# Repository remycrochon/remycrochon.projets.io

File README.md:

# Projets-Diy
Mise à disposition de mes projets conçus sous Eagle

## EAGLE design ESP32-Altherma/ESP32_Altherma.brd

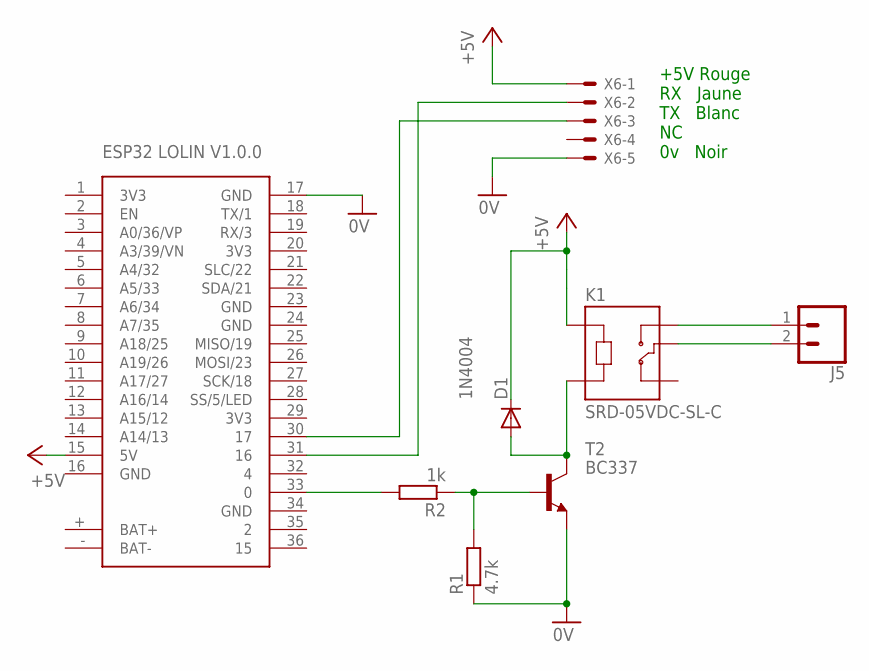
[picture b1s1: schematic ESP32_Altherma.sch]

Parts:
D1: 1N4004; DO41-10
J5: CONN_025MM; BORNIER_A_VIS_2_5.12MM
K1: SRD-05VDC-SL-C; RELAY_SRD-05VDC-SL-C
R1: 4.7k; 0207/10
R2: 1k; 0207/10
T2: BC337; TO92
U$4: ESP32_LOLIN_V1.0.0
X6: JST-XH-05-PIN-LONG-PAD; JST-XH-05-PACKAGE-LONG-PAD

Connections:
0V: R1.1, T2.1 (E), U$4.17 (GND), X6.5
3V3: U$4.1 (3V3), U$4.20 (3V3), U$4.29 (3V3)
+5V: D1.C, K1.A1, U$4.15 (5V), X6.1
BAT+: U$4.+ (BAT+)
BAT-: U$4.- (BAT-)
GND: U$4.16 (GND), U$4.23 (GND), U$4.24 (GND), U$4.34 (GND)
unnamed: D1.A, K1.A2, T2.3 (C)
unnamed: U$4.31 (16), X6.2
unnamed: U$4.30 (17), X6.3
unnamed: J5.1, K1.NO
unnamed: J5.2, K1.COM
unnamed: R1.2, R2.1, T2.2 (B)
unnamed: R2.2, U$4.33 (0)

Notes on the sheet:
+5V Rouge RX Jaune TX Blanc NC 0v Noir

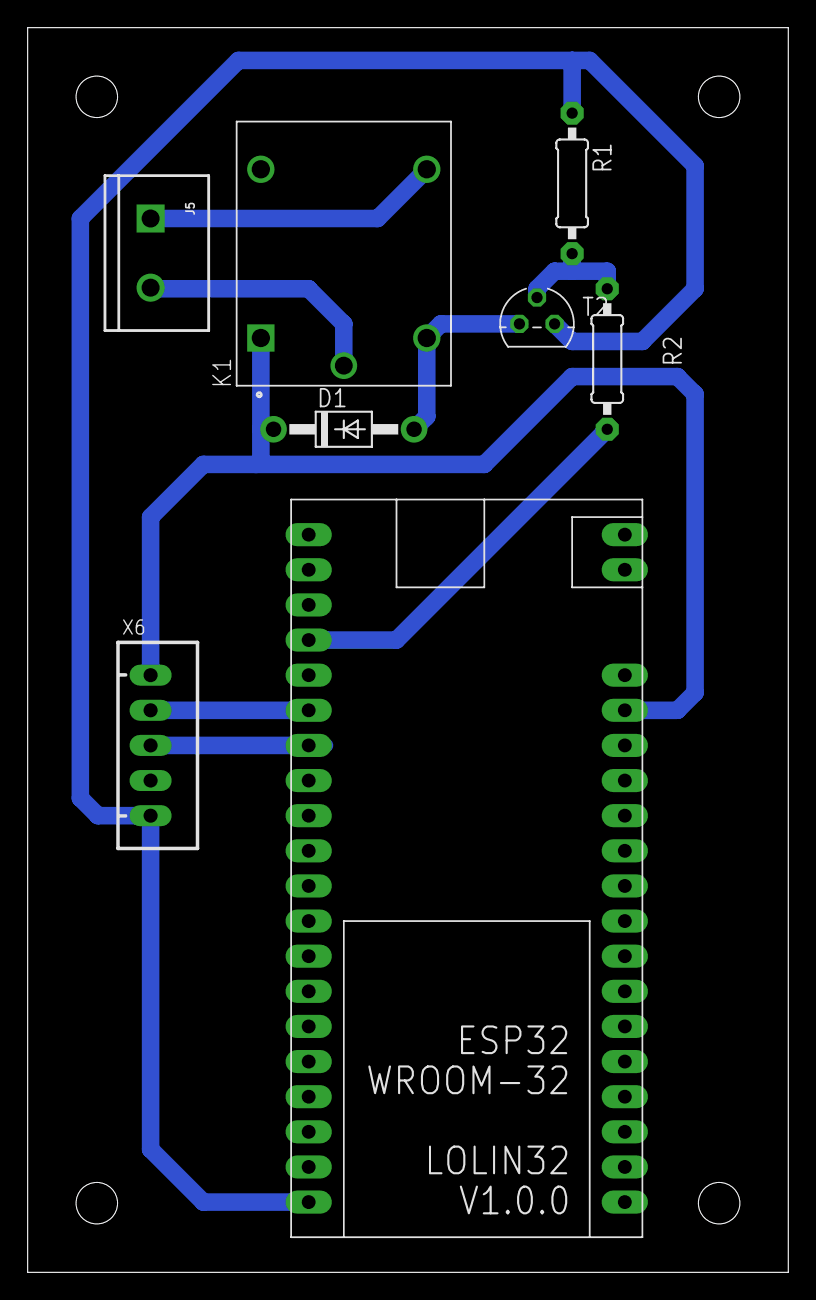
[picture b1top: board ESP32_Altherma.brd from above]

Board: 2 copper layers, 55.0 x 90.0 mm, 8 parts (0 on the bottom side), 11 nets.

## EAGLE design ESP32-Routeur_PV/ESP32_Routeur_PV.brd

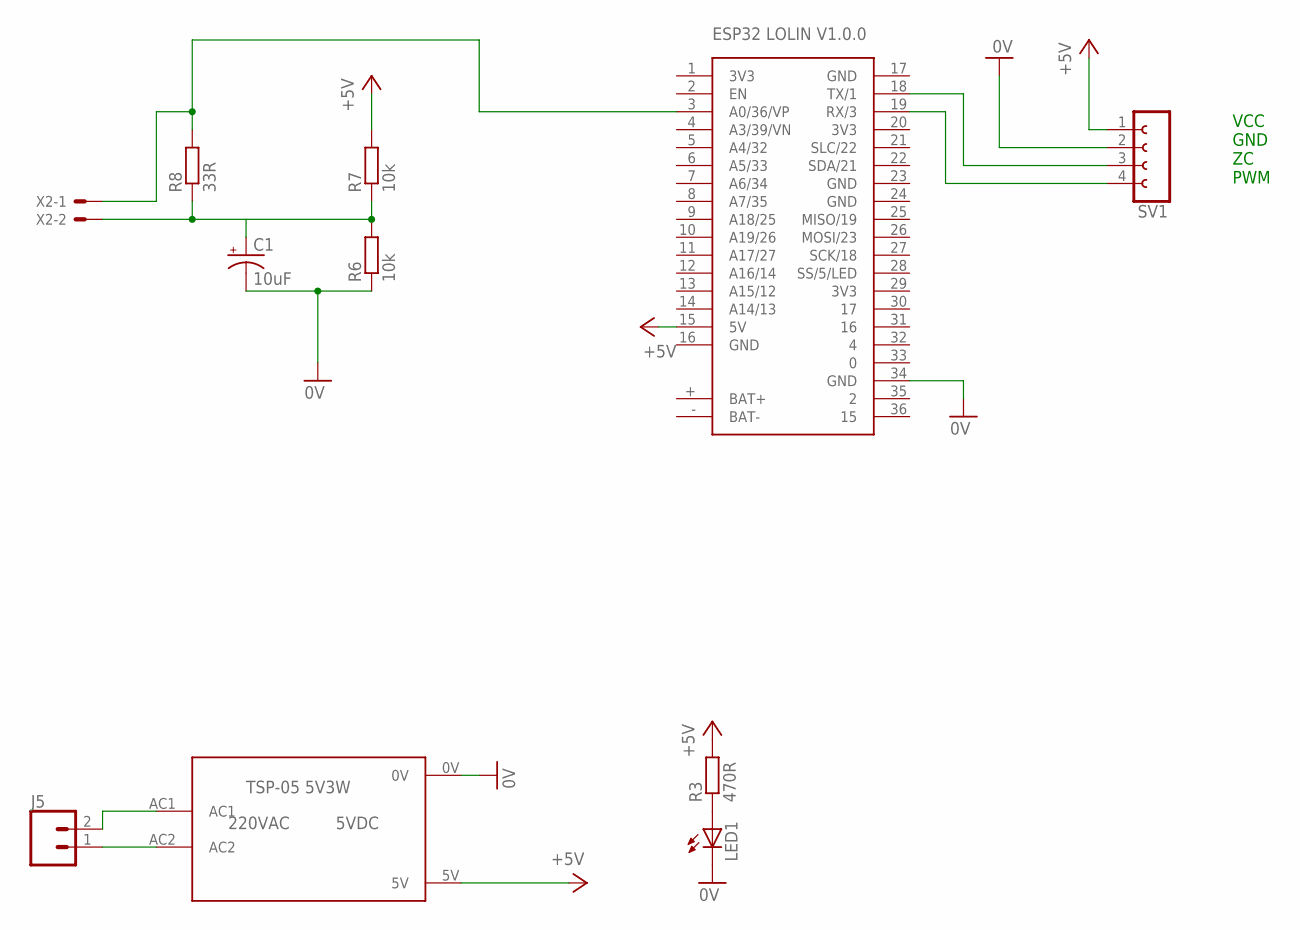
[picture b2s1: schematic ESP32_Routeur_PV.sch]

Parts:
C1: 10uF; CPOL-RADIAL-2.5MM-5MM
J5: CONN_025MM; BORNIER_A_VIS_2_5.12MM
LED1: LED5MM_F; LED5MM
R3: 470R; 0207/10
R6, R7: 10k; 0207/10
R8: 33R; 0207/10
SV1: FE04-1
U$3: TSP05-5V-3W
U$4: ESP32_LOLIN_V1.0.0
X2: JST-XH-02-PIN-LONG-PAD; JST-XH-02-PACKAGE-LONG-PAD

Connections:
0V: C1.2 (-), LED1.K (C), R6.1, SV1.2, U$3.0V, U$4.34 (GND)
3V3: U$4.1 (3V3), U$4.20 (3V3), U$4.29 (3V3)
+5V: R3.2, R7.2, SV1.1, U$3.5V, U$4.15 (5V)
BAT+: U$4.+ (BAT+)
BAT-: U$4.- (BAT-)
GND: U$4.16 (GND), U$4.17 (GND), U$4.23 (GND), U$4.24 (GND)
unnamed: LED1.A, R3.1
unnamed: C1.1 (+), R6.2, R7.1, R8.1, X2.2
unnamed: SV1.3, U$4.18 (TX/1)
unnamed: SV1.4, U$4.19 (RX/3)
unnamed: J5.2, U$3.AC1
unnamed: J5.1, U$3.AC2
unnamed: R8.2, U$4.3 (A0/36/VP), X2.1

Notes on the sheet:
VCC GND ZC PWM

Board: 2 copper layers, 11 parts (1 on the bottom side), 11 nets, no tracks yet.

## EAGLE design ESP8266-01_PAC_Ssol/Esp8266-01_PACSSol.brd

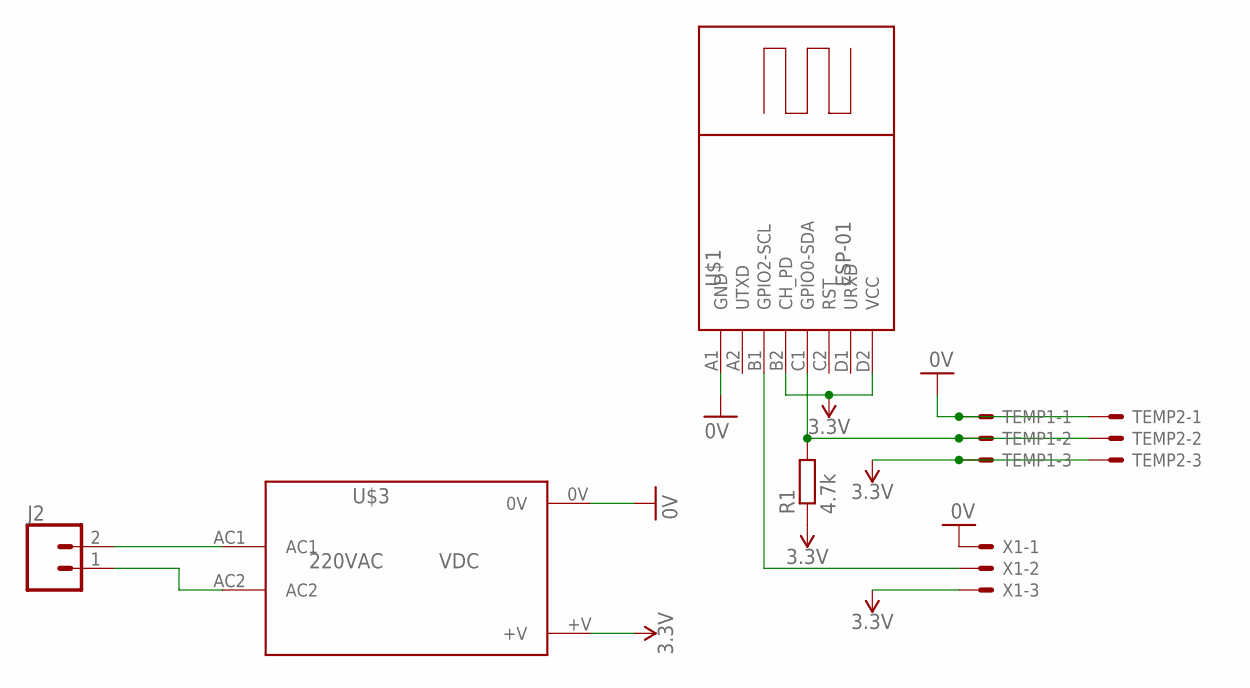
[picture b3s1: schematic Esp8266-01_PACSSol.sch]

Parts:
J2: CONN_025MM; BORNIER_A_VIS_2_5.12MM
R1: 4.7k; 0207/10
TEMP1, TEMP2: JST-XH-03-PIN-LONG-PAD; JST-XH-03-PACKAGE-LONG-PAD
U$1: ESP-01
U$3: TSP05-5V-3W; TSP05-VDC-3W
X1: JST-XH-03-PIN-LONG-PAD; JST-XH-03-PACKAGE-LONG-PAD

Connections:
0V: TEMP1.1, TEMP2.1, U$1.A1 (GND), U$3.0V, X1.1
3.3V: R1.1, TEMP1.3, TEMP2.3, U$1.B2 (CH_PD), U$1.D2 (VCC), U$3.+V, X1.3
unnamed: J2.2, U$3.AC1
unnamed: J2.1, U$3.AC2
unnamed: U$1.B1 (GPIO2-SCL), X1.2
unnamed: R1.2, TEMP1.2, TEMP2.2, U$1.C1 (GPIO0-SDA)

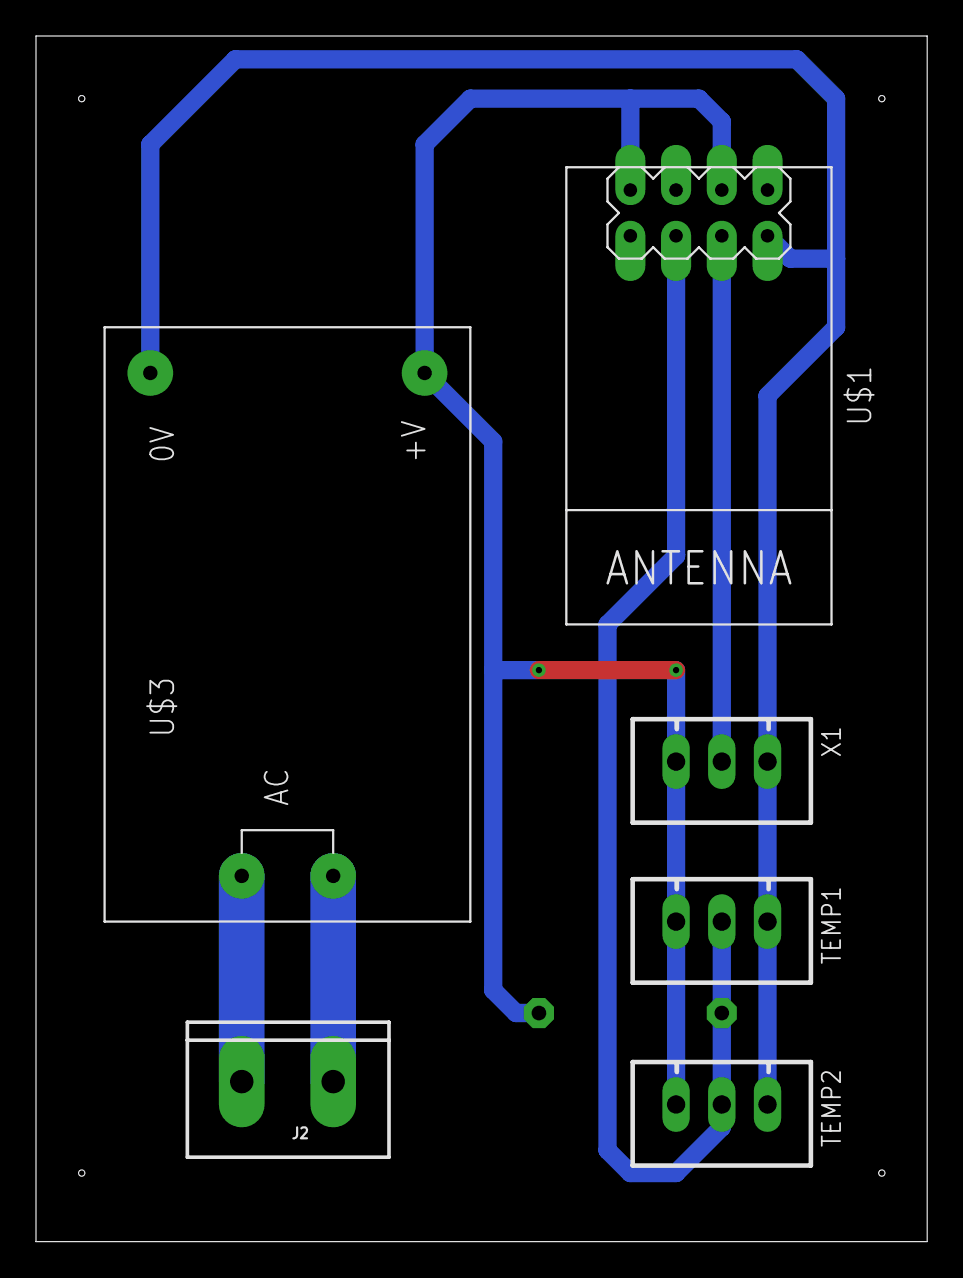
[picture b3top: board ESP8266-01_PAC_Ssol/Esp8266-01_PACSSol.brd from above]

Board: 2 copper layers, 49.5 x 67.0 mm, 7 parts (1 on the bottom side), 6 nets.

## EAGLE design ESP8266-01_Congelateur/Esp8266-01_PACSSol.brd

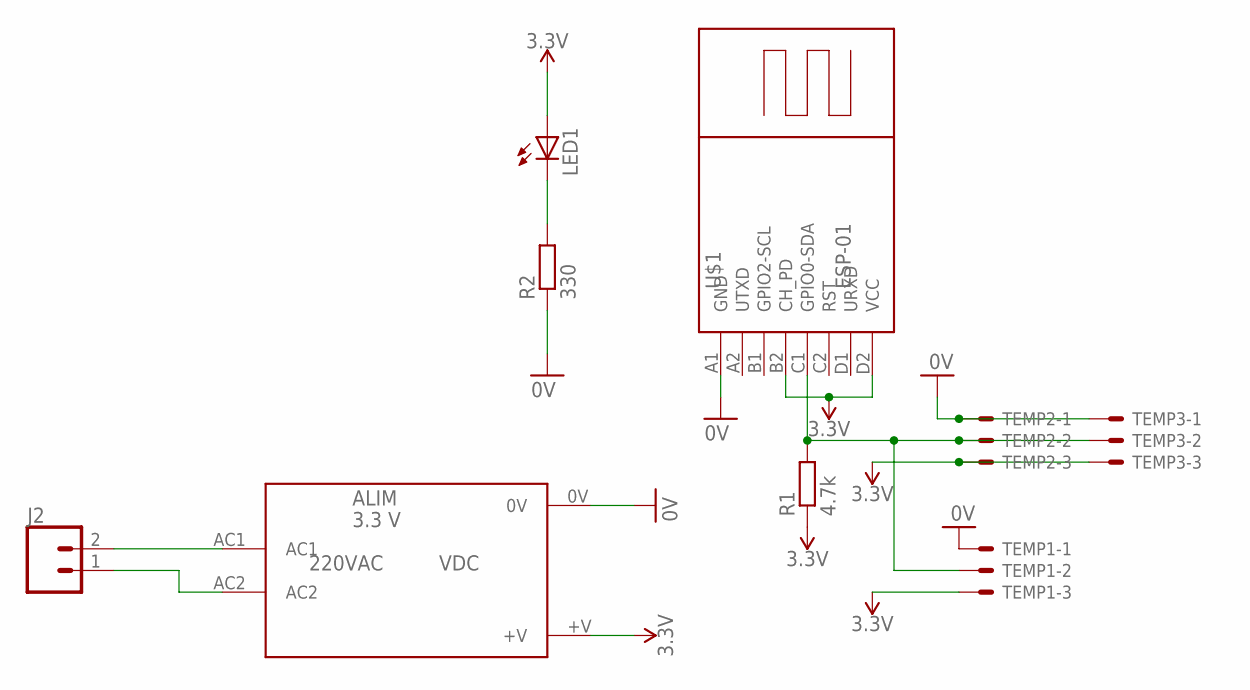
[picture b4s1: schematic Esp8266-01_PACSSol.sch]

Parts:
ALIM: 3.3 V; TSP05-VDC-3W
J2: CONN_025MM; BORNIER_A_VIS_2_5.12MM
LED1: LED5MM_F; LED5MM
R1: 4.7k; 0207/10
R2: 330; 0207/10
TEMP1, TEMP2, TEMP3: JST-XH-03-PIN-LONG-PAD; JST-XH-03-PACKAGE-LONG-PAD
U$1: ESP-01

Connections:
0V: ALIM.0V, R2.1, TEMP1.1, TEMP2.1, TEMP3.1, U$1.A1 (GND)
3.3V: ALIM.+V, LED1.A, R1.1, TEMP1.3, TEMP2.3, TEMP3.3, U$1.B2 (CH_PD), U$1.D2 (VCC)
unnamed: ALIM.AC1, J2.2
unnamed: ALIM.AC2, J2.1
unnamed: LED1.K (C), R2.2
unnamed: R1.2, TEMP1.2, TEMP2.2, TEMP3.2, U$1.C1 (GPIO0-SDA)

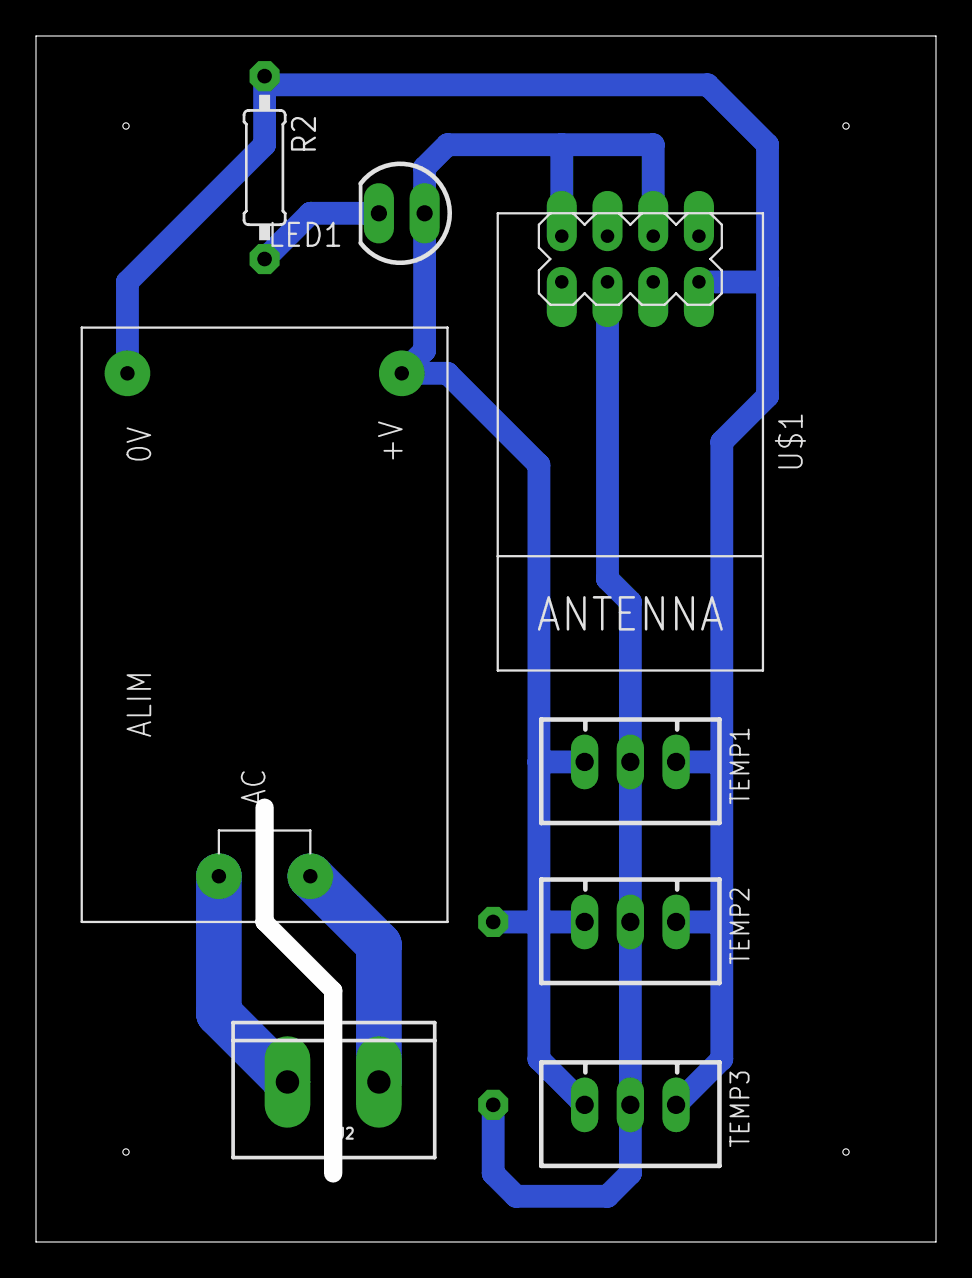
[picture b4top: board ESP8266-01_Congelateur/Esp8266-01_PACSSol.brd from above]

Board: 2 copper layers, 49.0 x 66.0 mm, 9 parts (1 on the bottom side), 6 nets.

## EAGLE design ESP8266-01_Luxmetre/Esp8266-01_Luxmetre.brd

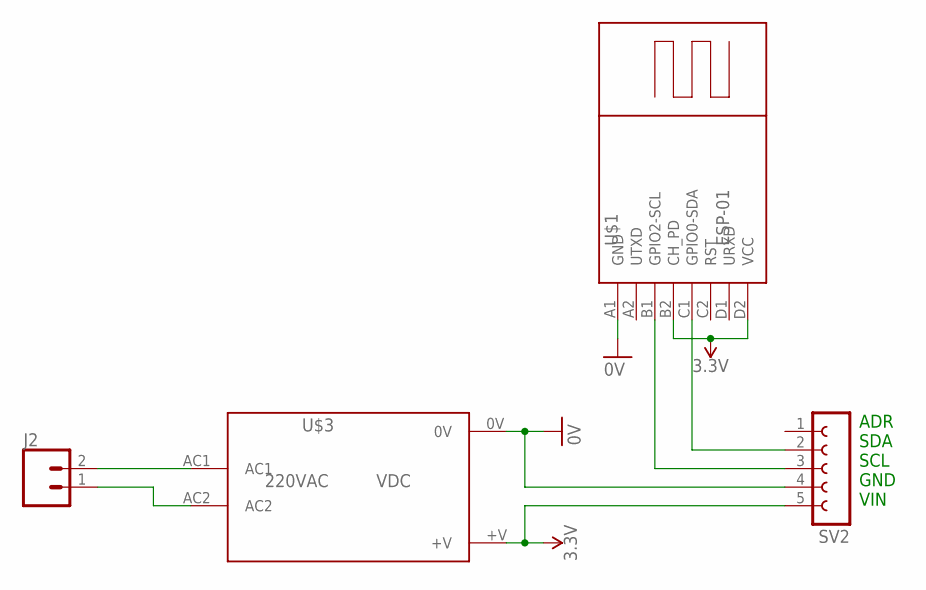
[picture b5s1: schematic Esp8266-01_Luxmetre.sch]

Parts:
J2: CONN_025MM; BORNIER_A_VIS_2_5.12MM
SV2: FE05-1
U$1: ESP-01
U$3: TSP05-5V-3W; TSP05-VDC-3W

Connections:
0V: SV2.4, U$1.A1 (GND), U$3.0V
3.3V: SV2.5, U$1.B2 (CH_PD), U$1.D2 (VCC), U$3.+V
unnamed: J2.2, U$3.AC1
unnamed: J2.1, U$3.AC2
unnamed: SV2.3, U$1.B1 (GPIO2-SCL)
unnamed: SV2.2, U$1.C1 (GPIO0-SDA)

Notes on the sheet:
ADR SDA SCL GND VIN

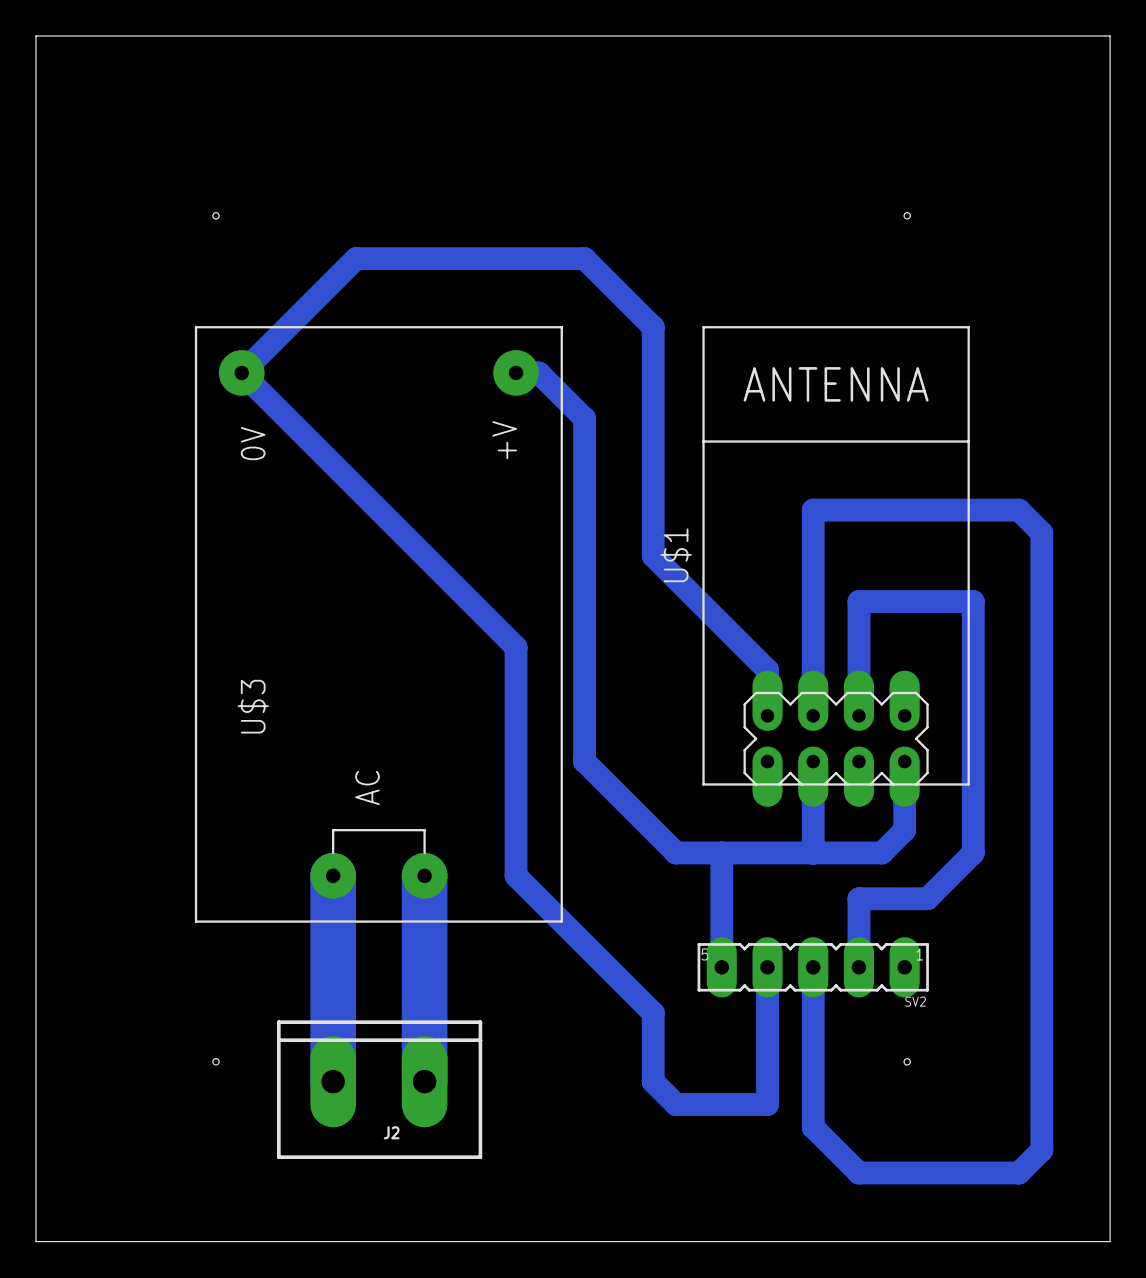
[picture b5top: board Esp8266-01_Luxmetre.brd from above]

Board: 2 copper layers, 59.7 x 67.0 mm, 4 parts (0 on the bottom side), 6 nets.

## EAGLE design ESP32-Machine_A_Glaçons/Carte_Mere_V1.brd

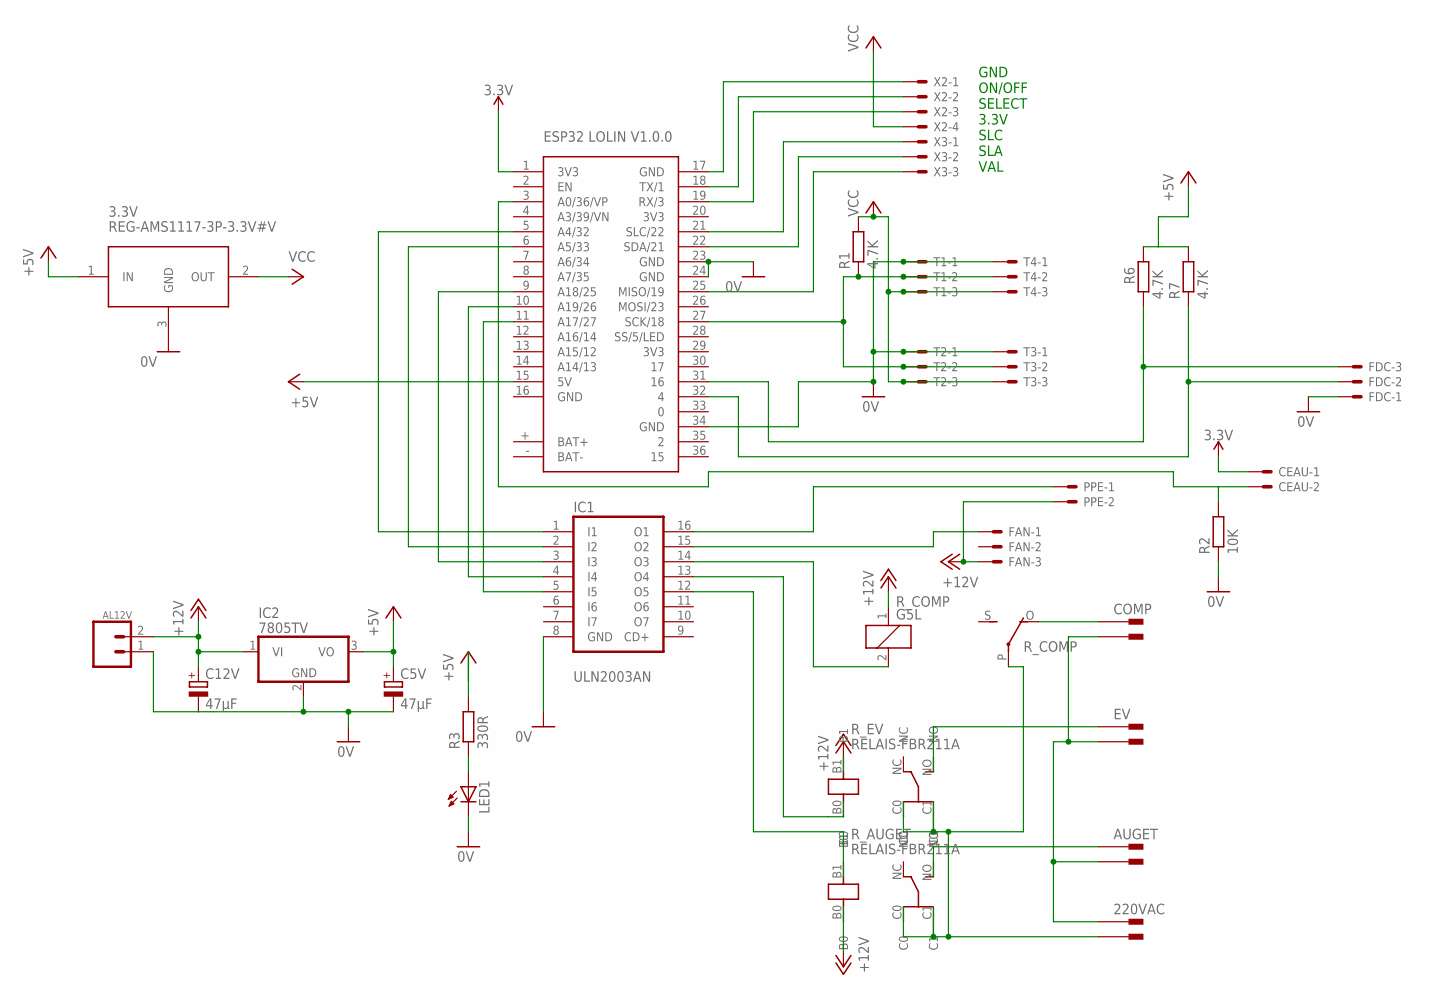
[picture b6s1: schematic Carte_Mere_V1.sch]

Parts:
3.3V: REG-AMS1117-3P-3.3V#V; REG-AMS1117-3P#V
220VAC, 220VAC_N: PIN2F061.040; F061.040
AL12V: CONN_025MM; BORNIER_A_VIS_2_5.12MM
AUGET: PIN2F061.040; F061.040
AUGET_N: PIN2F061.040; F061.040
C5V, C12V: 47µF; E2,5-5
CEAU: JST-XH-02-PIN-LONG-PAD; JST-XH-02-PACKAGE-LONG-PAD
COMP: PIN2F061.040; F061.040
COMP_N: PIN2F061.040; F061.040
EV: PIN2F061.040; F061.040
EV_N: PIN2F061.040; F061.040
FAN: JST-XH-03-PIN-LONG-PAD; JST-XH-03-PACKAGE-LONG-PAD
FDC: JST-XH-03-PIN-LONG-PAD; JST-XH-03-PACKAGE-LONG-PAD
IC1: ULN2003AN; DIL16
IC2: 7805TV; TO220V
LED1: LED5MM_F; LED5MM
PPE: JST-XH-02-PIN-LONG-PAD; JST-XH-02-PACKAGE-LONG-PAD
R1, R6, R7: 4.7K; 0207/10
R2: 10K; 0207/10
R3: 330R; 0207/10
R_AUGET: RELAIS-FBR211A
R_COMP: G5L; G5LE
R_EV: RELAIS-FBR211A
T1, T2, T3, T4: JST-XH-03-PIN-LONG-PAD; JST-XH-03-PACKAGE-LONG-PAD
U$1: ESP32_LOLIN_V1.0.0
X2: JST-XH-04-PIN-LONG-PAD; JST-XH-04-PACKAGE-LONG-PAD
X3: JST-XH-03-PIN-LONG-PAD; JST-XH-03-PACKAGE-LONG-PAD

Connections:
0V: 3.3V.3 (GND), AL12V.1, C5V.V-, C12V.V-, FDC.1, IC1.8 (GND), IC2.2 (GND), LED1.K (C), R2.1, T1.1, T2.1, T3.1, T4.1, U$1.23 (GND), U$1.24 (GND), U$1.34 (GND)
3.3V: CEAU.1, U$1.1 (3V3)
3V3: U$1.20 (3V3), U$1.29 (3V3)
+5V: 3.3V.1 (IN), C5V.V+, IC2.3 (VO), R3.2, R6.2, R7.2, U$1.15 (5V)
+12V: AL12V.2, C12V.V+, FAN.3, IC2.1 (VI), PPE.2, R_AUGET.B0, R_COMP.1, R_EV.B1
BAT+: U$1.+ (BAT+)
BAT-: U$1.- (BAT-)
GND: U$1.16 (GND)
unnamed: U$1.21 (SLC/22), X3.1
unnamed: EV.A1, EV.A2, R_EV.NO
unnamed: IC1.1 (I1), U$1.5 (A4/32)
unnamed: FDC.2, R7.1, U$1.32 (4)
unnamed: IC1.2 (I2), U$1.6 (A5/33)
unnamed: LED1.A, R3.1
unnamed: IC1.16 (O1), PPE.1
unnamed: FAN.1, IC1.15 (O2)
unnamed: IC1.14 (O3), R_COMP.2
unnamed: IC1.3 (I3), U$1.9 (A18/25)
unnamed: IC1.4 (I4), U$1.10 (A19/26)
unnamed: IC1.5 (I5), U$1.11 (A17/27)
unnamed: IC1.13 (O4), R_EV.B0
unnamed: IC1.12 (O5), R_AUGET.B1
unnamed: 220VAC.A1, 220VAC.A2, AUGET_N.A1, AUGET_N.A2, COMP_N.A1, COMP_N.A2, EV_N.A1, EV_N.A2
unnamed: U$1.22 (SDA/21), X3.2
unnamed: AUGET.A1, AUGET.A2, R_AUGET.NO
unnamed: COMP.A1, COMP.A2, R_COMP.O
unnamed: 220VAC_N.A1, 220VAC_N.A2, R_AUGET.C0, R_AUGET.C1, R_COMP.P, R_EV.C0, R_EV.C1
unnamed: U$1.17 (GND), X2.1
unnamed: FDC.3, R6.1, U$1.31 (16)
unnamed: U$1.18 (TX/1), X2.2
unnamed: U$1.19 (RX/3), X2.3
unnamed: U$1.25 (MISO/19), X3.3
unnamed: CEAU.2, R2.2, U$1.3 (A0/36/VP)
unnamed: R1.1, T1.2, T2.2, T3.2, T4.2, U$1.27 (SCK/18)
VCC: 3.3V.2 (OUT), R1.2, T1.3, T2.3, T3.3, T4.3, X2.4

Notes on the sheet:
GND ON/OFF SELECT 3.3V SLC SLA VAL

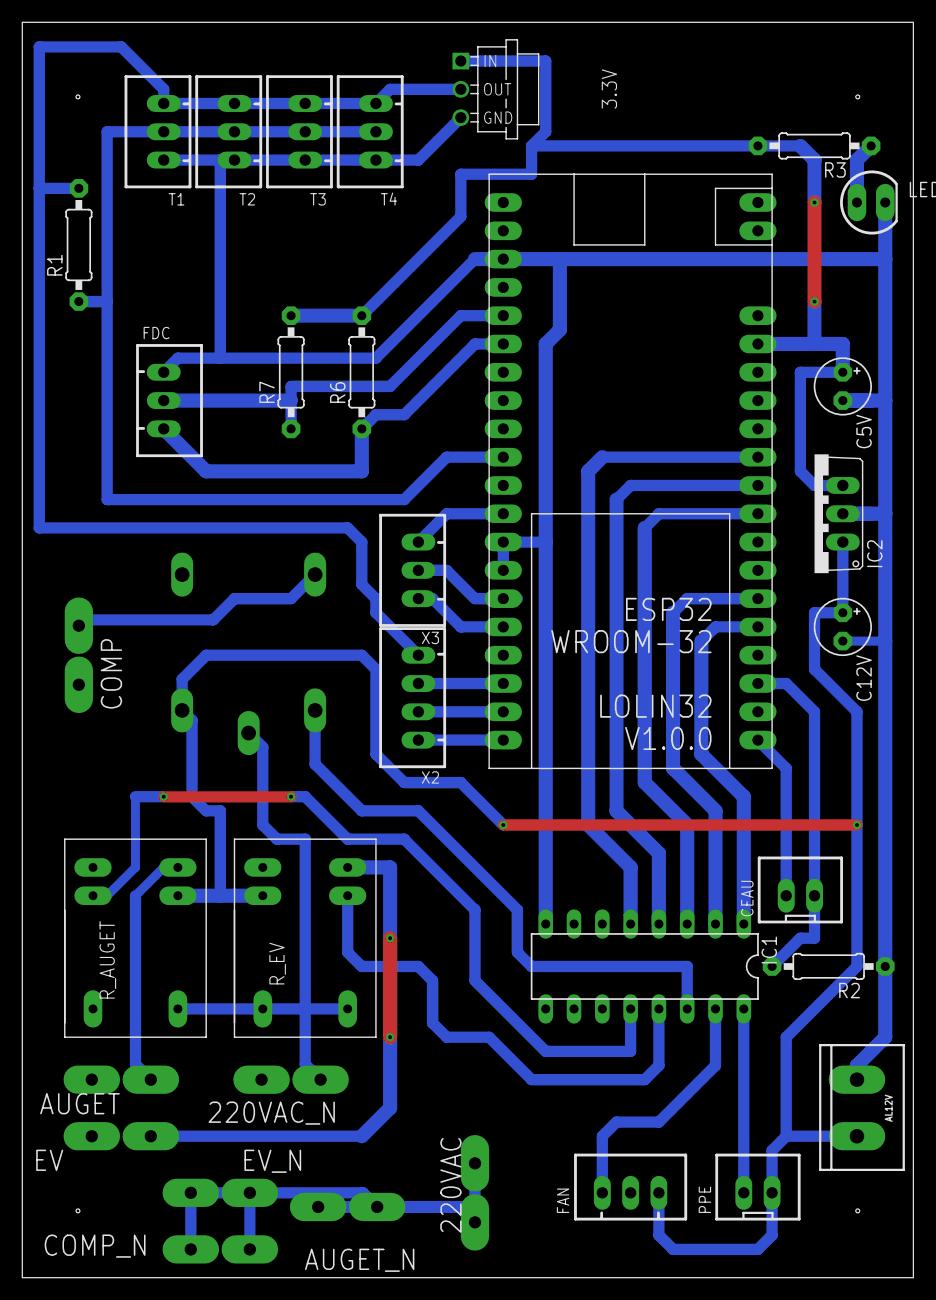
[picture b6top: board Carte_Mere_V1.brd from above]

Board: 2 copper layers, 80.0 x 112.7 mm, 34 parts (1 on the bottom side), 32 nets.

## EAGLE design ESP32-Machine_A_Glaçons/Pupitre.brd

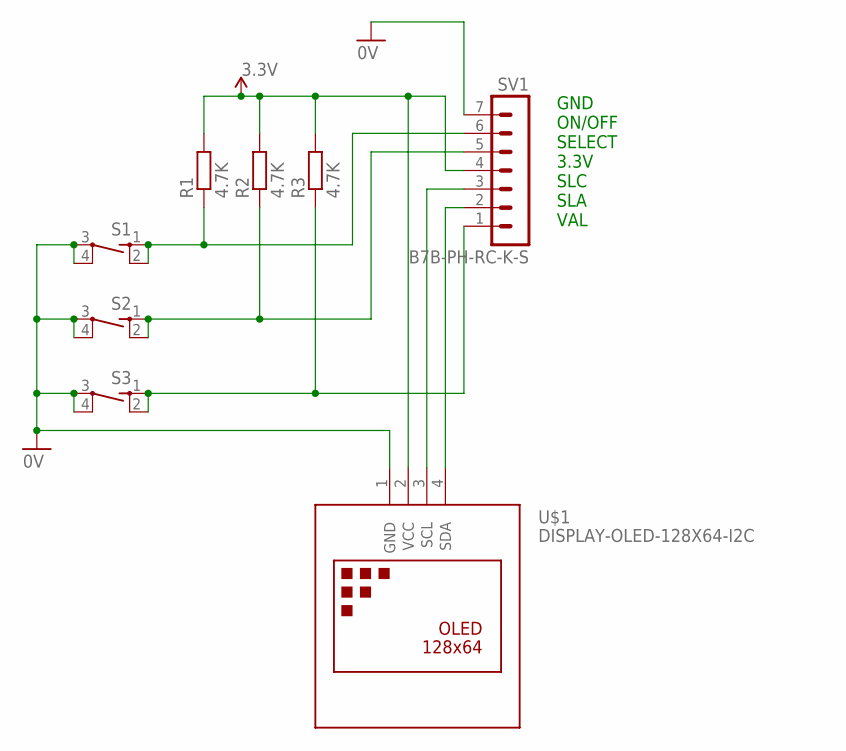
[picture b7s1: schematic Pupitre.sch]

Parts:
R1, R2, R3: 4.7K; 0207/10
S1, S2, S3: SWITCH_10-XX; SWITCH-10XX
SV1: B7B-PH-RC-K-S; B7B-PH-K-S
U$1: DISPLAY-OLED-128X64-I2C

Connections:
0V: S1.3, S1.4 (P1), S2.3, S2.4 (P1), S3.3, S3.4 (P1), SV1.7, U$1.1 (GND)
unnamed: R3.1, S3.1 (S), S3.2 (S1), SV1.1
unnamed: R2.1, S2.1 (S), S2.2 (S1), SV1.5
unnamed: R1.1, S1.1 (S), S1.2 (S1), SV1.6
unnamed: R1.2, R2.2, R3.2, SV1.4, U$1.2 (VCC)
unnamed: SV1.2, U$1.4 (SDA)
unnamed: SV1.3, U$1.3 (SCL)

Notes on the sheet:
GND ON/OFF SELECT 3.3V SLC SLA VAL

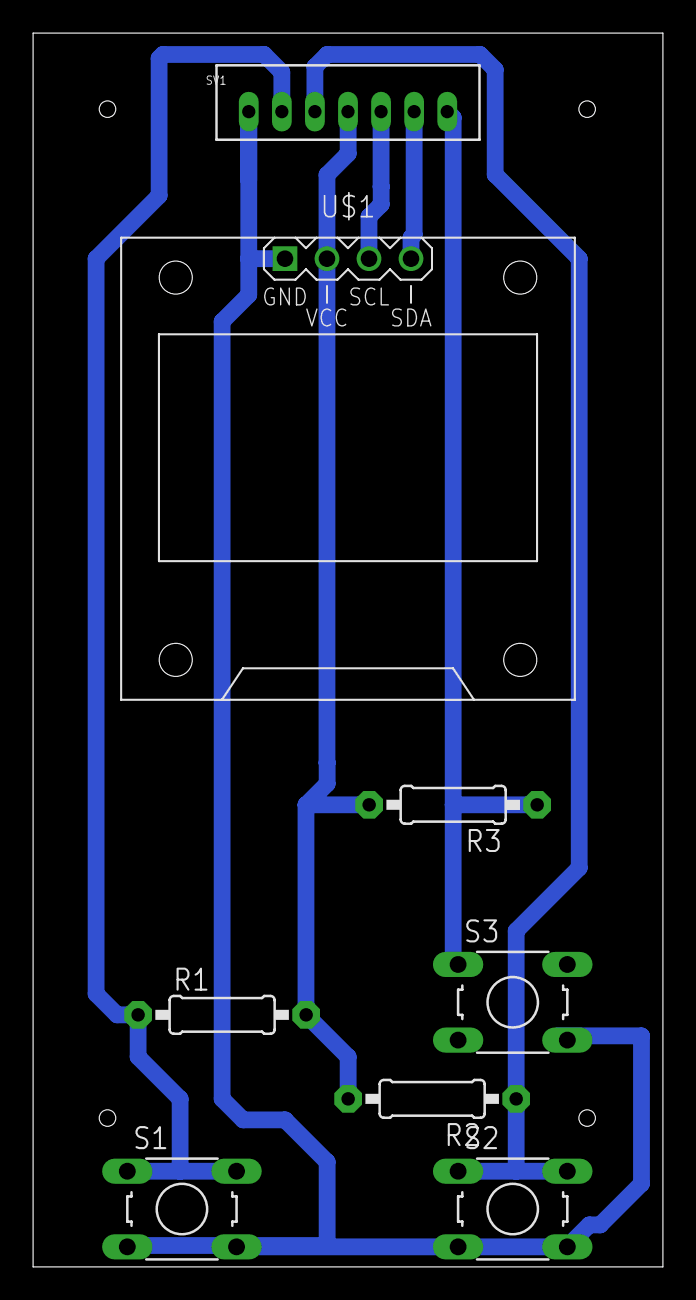
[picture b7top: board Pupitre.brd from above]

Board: 2 copper layers, 38.1 x 74.6 mm, 8 parts (0 on the bottom side), 7 nets.

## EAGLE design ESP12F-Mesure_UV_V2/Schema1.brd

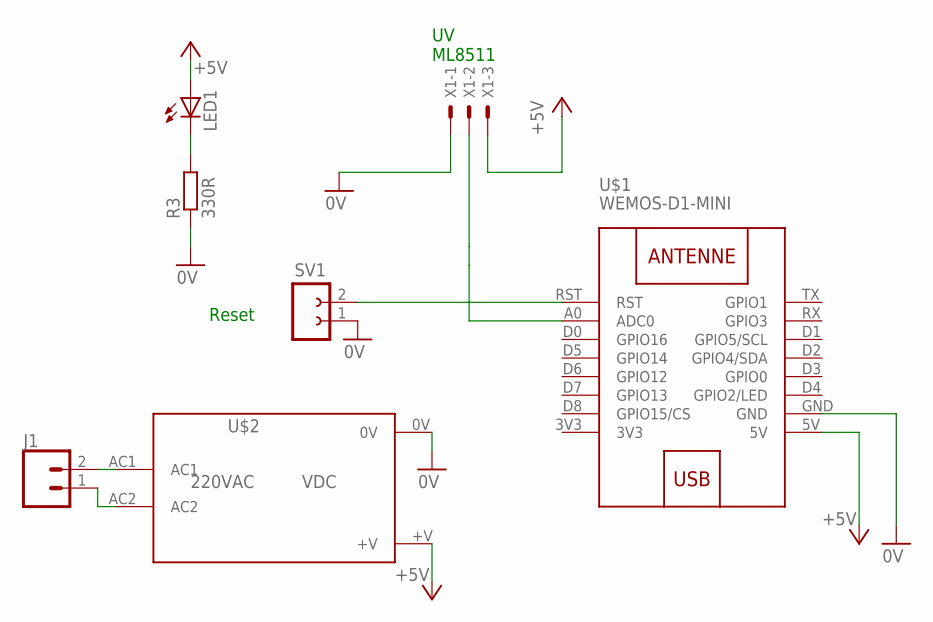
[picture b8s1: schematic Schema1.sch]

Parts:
J1: CONN_025MM; BORNIER_A_VIS_2_5.12MM
LED1: LED5MM_F; LED5MM
R3: 330R; 0207/10
SV1: FE02-1
U$1: WEMOS-D1-MINI
U$2: TSP05-5V-3W; TSP05-VDC-3W
X1: JST-XH-03-PIN-LONG-PAD; JST-XH-03-PACKAGE-LONG-PAD

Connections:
0V: R3.1, SV1.1, U$1.GND, U$2.0V, X1.1
3V3: U$1.3V3
+5V: LED1.A, U$1.5V, U$2.+V, X1.3
unnamed: U$1.A0 (ADC0), X1.2
unnamed: J1.2, U$2.AC1
unnamed: SV1.2, U$1.RST
unnamed: J1.1, U$2.AC2
unnamed: LED1.K (C), R3.2

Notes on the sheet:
Reset
UV ML8511

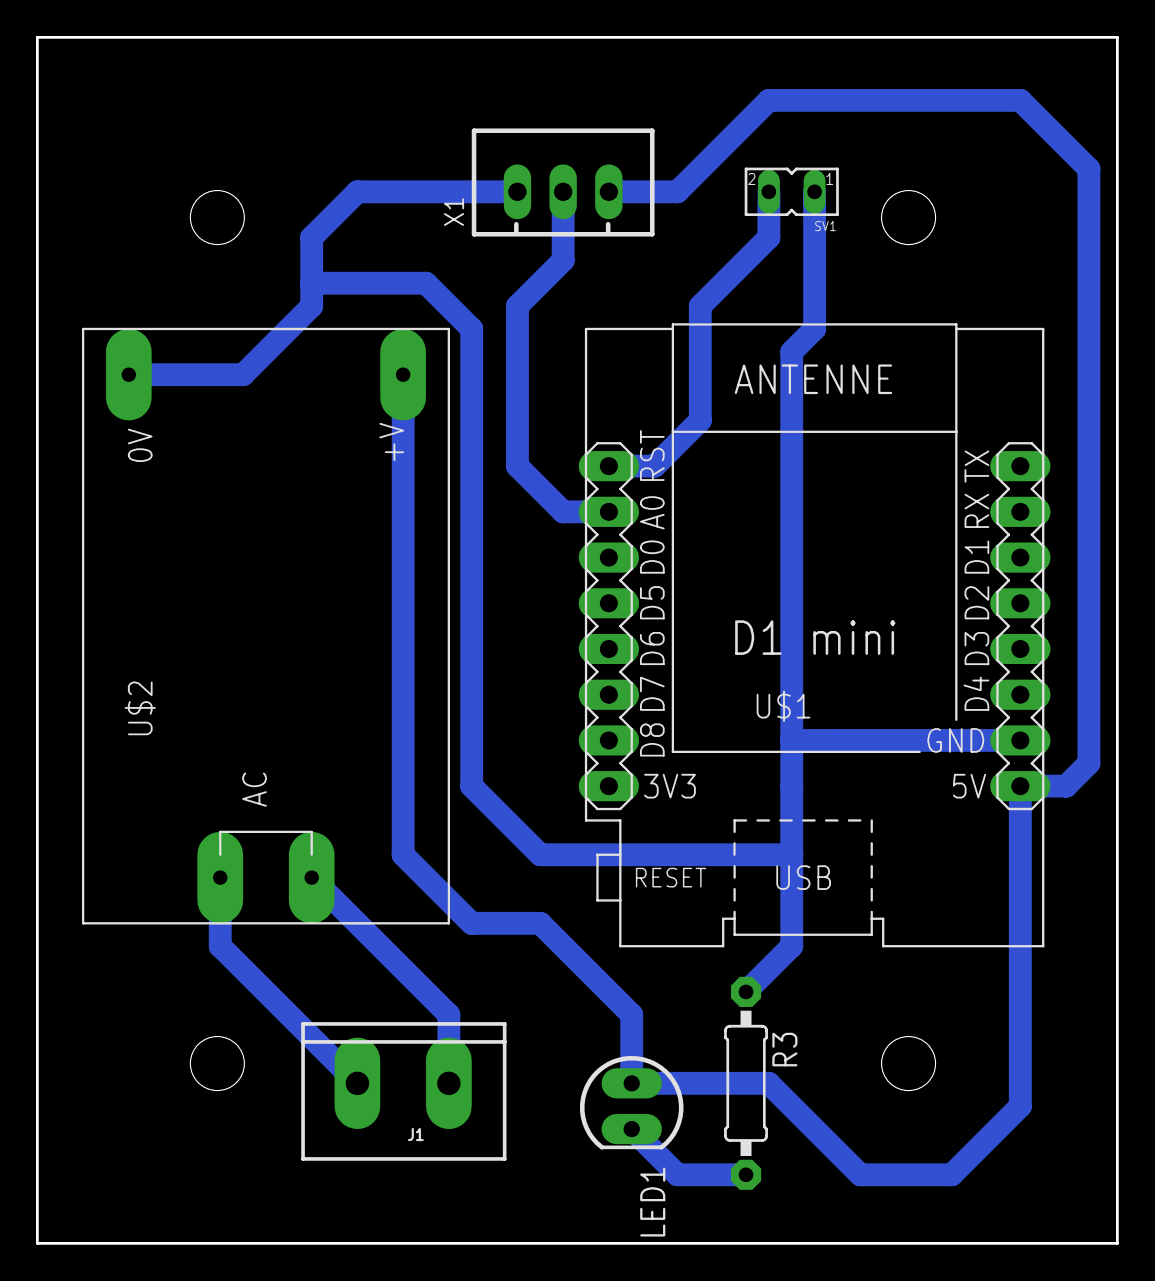
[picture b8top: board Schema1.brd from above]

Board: 2 copper layers, 60.0 x 67.0 mm, 7 parts (0 on the bottom side), 7 nets.

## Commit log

2022-03-15 config files on 15-03-2022 14:39:50
2022-03-15 config files on 15-03-2022 14:42:14
2022-03-15 config files on 15-03-2022 14:45:59
2022-03-15 config files on 15-03-2022 14:49:42
2022-03-15 config files on 15-03-2022 14:52:12
2022-03-15 config files on 15-03-2022 14:53:43
2022-03-15 config files on 15-03-2022 14:56:00
2022-03-15 config files on 15-03-2022 14:56:45
2022-03-15 config files on 15-03-2022 15:00:49
2022-03-15 config files on 15-03-2022 15:01:46
2022-03-15 config files on 15-03-2022 15:03:12
2022-03-15 config files on 15-03-2022 15:05:25
2022-03-15 config files on 15-03-2022 15:07:02
2022-03-15 config files on 15-03-2022 15:09:10
2022-03-15 config files on 15-03-2022 15:09:23
2022-03-15 config files on 15-03-2022 15:10:00
2022-03-15 config files on 15-03-2022 15:12:40
2022-03-15 config files on 15-03-2022 15:15:23
2022-03-15 config files on 15-03-2022 15:16:34
2022-03-15 config files on 15-03-2022 15:16:57
2022-03-15 config files on 15-03-2022 15:25:07
2022-03-15 config files on 15-03-2022 15:27:57
2022-03-15 config files on 15-03-2022 15:28:56
2022-03-15 config files on 15-03-2022 15:29:50
2022-03-15 config files on 15-03-2022 15:30:57
2022-03-15 config files on 15-03-2022 15:31:28
2022-03-15 config files on 15-03-2022 15:31:37
2022-03-15 config files on 15-03-2022 15:32:40
2022-03-15 config files on 15-03-2022 15:47:54

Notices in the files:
parts and their libraries:
05-arduino_etc: Released under the Creative Commons Attribution 4.0 International License: http://creativecommons.org/licenses/by/4.0
SparkFun-PowerSymbols: Licensing: Creative Commons ShareAlike 4.0 International - https://creativecommons.org/licenses/by-sa/4.0
